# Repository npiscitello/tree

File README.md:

# tree
Code for a blinky palm tree, which is really just a long strip of fairy lights
bent up in the shape of a palm tree. The fairy lights are wired as a bunch of
parallel LEDs with alternating polarity, so by switching the polarity, you
switch the set of lights that are lit. Poke some MOSFETs into an ATMEGA328 and
you have yourself some good old-fashioned blinkenlight!

Check out [avr-libc] (https://nongnu.org/avr-libc/) for the libs I use.

# dimming profiles
I decided I didn't like a strictly linear dim, so I played around with some
custom dimming profiles, implemented as a lookup table. Turns out, it starts
looking weird if you stray too far from linear, so I settled on the
circular_mod profile. This is, of course, for my sister, so if she doesn't like
it I'll keep tweaking! See the ODS spreadsheet for calculation details.
Remember, since we're using inverted PWM, an output of 255 is off and 0 is
fully on.

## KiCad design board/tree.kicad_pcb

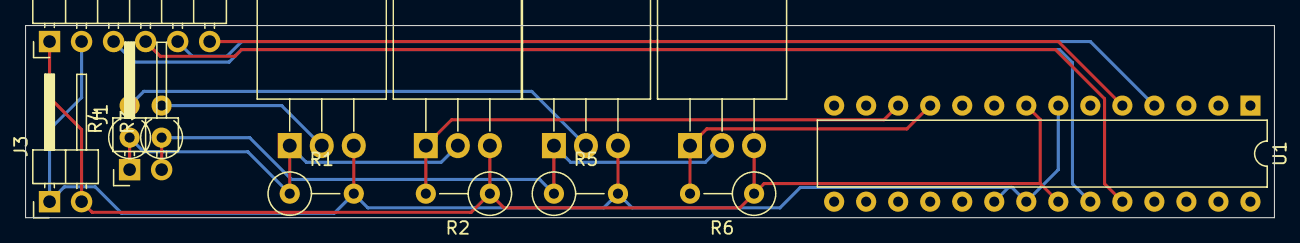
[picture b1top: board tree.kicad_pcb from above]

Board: 2 copper layers, 99.1 x 15.2 mm, 14 parts (0 on the bottom side), 12 nets.

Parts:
J1: LED; PinHeader_1x02_P2.54mm_Horizontal
J2: panel; PinHeader_1x06_P2.54mm_Horizontal
J3: PWR; PinHeader_1x02_P2.54mm_Horizontal
Q1, Q3: PMOS; TO-220-3_Horizontal_TabDown
Q2, Q4: NMOS; TO-220-3_Horizontal_TabDown
R1, R2, R5, R6: 33k; R_Axial_DIN0309_L9.0mm_D3.2mm_P5.08mm_Vertical
R3, R4: 10; R_Axial_DIN0309_L9.0mm_D3.2mm_P2.54mm_Vertical
U1: ATmega328-PU; DIP-28_W7.62mm

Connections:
+5V: J2.2, J3.1, Q1.3, Q3.3, R1.2, R5.2, U1.7, U1.20, U1.21
/blink: J2.6, U1.5
/bright: J2.3, U1.23
/fade: J2.5, U1.4
/led_A: Q2.1, R2.2, U1.12
/led_B: Q4.1, R6.2, U1.11
/speed: J2.4, U1.24
GND: J2.1, J3.2, Q2.3, Q4.3, R2.1, R6.1, U1.8, U1.22
unnamed: J1.1, Q1.1, Q2.2, R1.1, R4.1
unnamed: J1.2, Q3.1, Q4.2, R3.1, R5.1
unnamed: Q1.2, R3.2
unnamed: Q3.2, R4.2

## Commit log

2020-11-27 set up compilation
2020-11-28 steady on mode works...in one iteration :)
2020-11-28 all lights are on now! pretty
2020-11-28 always on mode with brightness control works
2020-11-28 added ADC swapping to prep for speed control for patterns
2020-11-28 blink mode is a go
2020-11-29 trying a restructure, getting very weird errors. Commiting so I can revert and see if they're present previously
2020-11-29 back to working - problem was a lack of understanding of how PWM works
2020-11-29 Trying a slower clock (2MHz)
    This will allow a PWM freq of 976, doubled from previous, and an
    effective PWM freq of 488 - high enough to avoid flickering and low
    enough to play nice with the MOSFETs. Hopefully. This is something
    that'll just have to be tested on the final board.
    Also reassigned bank switching duty to the TIM0 interrupt.
2020-11-29 stubbed out fade timing and method
2020-11-29 seems to glitch out unless blink is run first...
2020-12-05 constant rate fade implemented, speeds up as brightness decreases. TODO: constant time fade
2020-12-05 constant time fade implemented
2020-12-05 tried math-based variable rate fade, too slow; going to a lookup table
2020-12-06 lookup-driven fade is working! Code should be done, just need to make a board and test it
2020-12-06 docs...of a sort
2020-12-06 more docs...of a sort
2020-12-27 just cleaning up - was chasing an error that ended up being a lack of a filter cap -.-
2021-07-04 added physcial designs
